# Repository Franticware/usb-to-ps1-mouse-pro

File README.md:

# usb-to-ps1-mouse-pro

This is an adapter for connecting USB mouse to PS1. It emulates the original [SCPH-1090 PlayStation Mouse](https://en.wikipedia.org/wiki/PlayStation_Mouse).

It can also convert [keyboard key presses to controller button presses](https://franticware.github.io/usb-to-ps1-mouse-pro/keyboard.html).

## Availability

[Check here](https://www.franticware.com/usb-to-ps1-mouse-pro-availability) whether the adapter is available for purchase.

## Firmware

The firmware is written mostly in C. It depends on [Raspberry Pi Pico SDK](https://github.com/raspberrypi/pico-sdk).

For a guide on how to update the firmware, see [Flashing the Firmware](https://franticware.github.io/usb-to-ps1-mouse-pro/flashing.html).

## Hardware

See [kicad](kicad) subdirectory for schematics and PCB design files. Alternatively, check [wiring](wiring) subdirectory for laymen-friendly picture guide or if you are looking to rewire your older [usb-to-playstation-mouse](https://github.com/Franticware/usb-to-playstation-mouse) adapter.

## Enclosure

The enclosure is intended for the PCB-based variant. The handwired one will not fit.

Printing in clear PETG is recommended.

3D model: https://www.printables.com/model/914178-official-enclosure-for-usb-to-ps1-mouse-pro

## Notes

* Important:
  * Make sure the USB device is rated for 100 mA or less (most USB mice and keyboards are). Do not connect devices with higher (or unspecified) current draw.
* Known issues:
  * Fixed in PCB_3: Incompatible with PSOne (SCPH-10X), where there are issues such as game stuttering and console reset.
  * In rare cases, Lemmings might pause during gameplay.
  * USB mouse compatibility is not 100%. The same applies to USB keyboards.
* Gameplay video:

## References - GitHub

This project would not be possible without these. Please go give them a star.

https://github.com/sekigon-gonnoc/Pico-PIO-USB

https://github.com/listff/hidparser

## Support this project

To help this project, you can go listen to or even buy a [music track of mine](https://share.amuse.io/track/vojtech-salajka-color-graphics-pinball-original-game-soundtrack) via your favorite service. It is not much, but it is the only digital product I am currently offering commercially as of writing this. Thank you!

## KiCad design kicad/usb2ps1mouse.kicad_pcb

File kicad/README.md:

## BOM

|Reference|Value|Datasheet|Footprint|Qty||
|-|-|-|-|-|-|
|C1, C2|10u/16V|~|Capacitor_SMD:C_1206_3216Metric|2||
|J1|Conn_01x09_Pin|~|PS1:Controller_THT90|1||
|J2|USB_A| ~|usb2ps1mouse-specific:USB_A_Sunken|1||
|J3|Conn_01x02|~|Jumper:SolderJumper-2_P1.3mm_Open_RoundedPad1.0x1.5mm|1|Short|
|J4|Conn_01x02|~|Jumper:SolderJumper-2_P1.3mm_Open_RoundedPad1.0x1.5mm|1|Do not short|
|R1, R2|22R|~|Resistor_SMD:R_0603_1608Metric|2||
|U1|RP2040-Zero||RP2040_Board:RP2040-Zero|1||
|U3|AMS1117-5.0|http://www.advanced-monolithic.com/pdf/ds1117.pdf|Package_TO_SOT_SMD:SOT-223-3_TabPin2|1||
||M3x10 countersunk screw + M3 nut|||1+1||

## Manufacturing

I have had the boards made at https://jlcpcb.com using the following parameters:

- PCB Thickness: 1.6
- PCB Color: Black
- Silkscreen: White
- Material Type: FR4
- Via Covering: Tented
- Surface Finish: LeadFree HASL
- Outer Copper Weight: 1 oz
- Board Outline Tolerance: ±0.2mm (Regular)

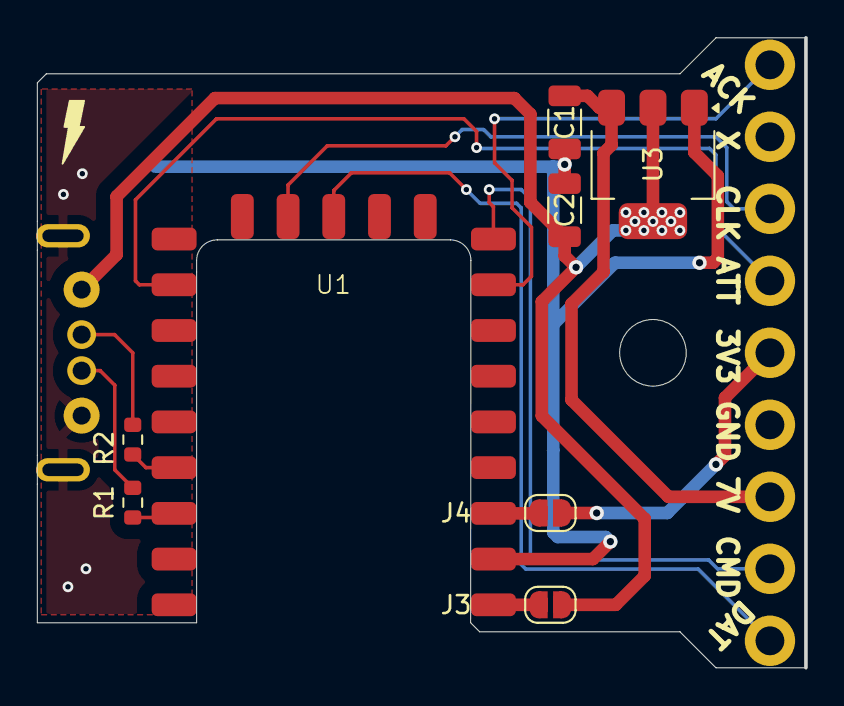
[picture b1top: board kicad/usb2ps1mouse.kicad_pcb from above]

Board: 2 copper layers, 42.6 x 35.0 mm, 11 parts (1 on the bottom side), 15 nets.

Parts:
C1, C2: 10u/16V; C_1206_3216Metric
H1: MountingHole; MountingHole_3.7mm
J1: Conn_01x09_Pin; Controller_THT90
J2: USB_A; USB_A_Sunken
J3, J4: Conn_01x02; SolderJumper-2_P1.3mm_Open_RoundedPad1.0x1.5mm
R1, R2: 22R; R_0603_1608Metric
U1: RP2040-Zero
U3: AMS1117-5.0; SOT-223-3_TabPin2

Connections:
+5V: C2.1, J2.1 (VBUS), J3.1, U3.2 (VO)
ACK: J1.9, U1.16 (15)
ATT: J1.6, U1.8 (7)
CLK: J1.7, U1.11 (10)
CMD: J1.2, U1.15 (14)
DATA: J1.1, U1.12 (11)
DM: J2.2 (D-), R2.1
DP: J2.3 (D+), R1.1
GND: C1.2, C2.2, J1.4, J2.4 (GND), J2.5 (Shield), U1.22 (GND), U3.1 (GND)
unnamed: J3.2, U1.23 (5V)
unnamed: J4.2, U1.21 (3V3)
unnamed: R1.2, U1.3 (2)
unnamed: R2.2, U1.4 (3)
VCON: J1.5, J4.1
VMOT: C1.1, J1.3, U3.3 (VI)

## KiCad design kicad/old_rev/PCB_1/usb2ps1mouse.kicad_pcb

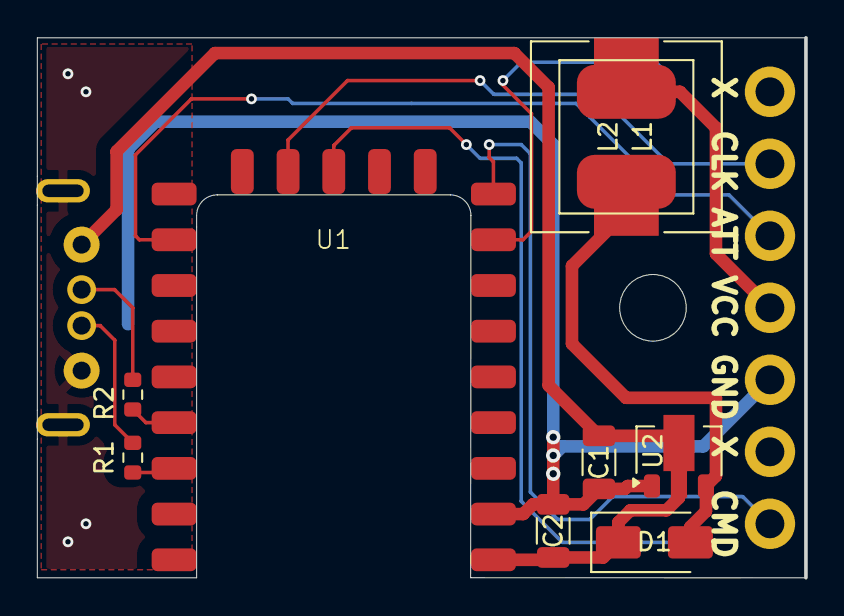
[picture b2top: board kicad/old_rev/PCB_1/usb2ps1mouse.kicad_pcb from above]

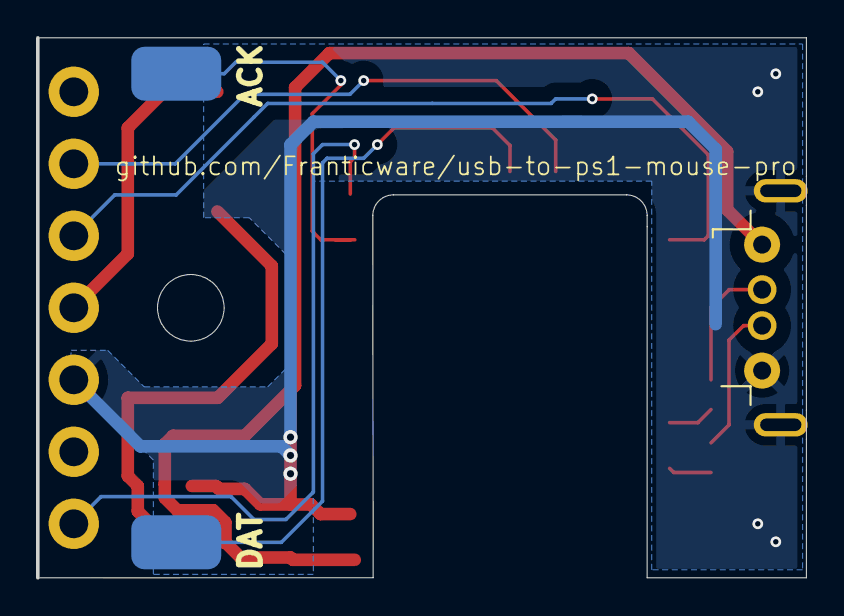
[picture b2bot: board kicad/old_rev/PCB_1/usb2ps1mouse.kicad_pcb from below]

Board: 2 copper layers, 42.6 x 30.0 mm, 14 parts (3 on the bottom side), 13 nets.

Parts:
C1, C2: 10u/16V; C_1206_3216Metric
D1: SS14; D_SMA
H1: MountingHole; MountingHole_3.7mm
J1: Conn_01x07_Pin; Controller_THT90
J2, J3: Conn_01x01_Pin; DSCON_pad
J4: USB_A; USB_A_Sunken
L1: 220; L_10.4x10.4_H4.8
L2: 220; L_Sumida_CR75
R1, R2: 22R; R_0603_1608Metric
U1: RP2040-Zero
U2: ME2108A50PG; SOT-89-3

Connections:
+5V: C1.1, C2.1, D1.1 (K), J4.1 (VBUS), U1.23 (5V), U2.2 (Vout)
ACK: J2.1, U1.16 (15)
ATT: J1.5, U1.8 (7)
CLK: J1.6, U1.11 (10)
CMD: J1.1, U1.15 (14)
DATA: J3.1, U1.12 (11)
DM: J4.2 (D-), R2.1
DP: J4.3 (D+), R1.1
GND: C1.2, C2.2, J1.3, J4.4 (GND), J4.5 (Shield), U1.22 (GND), U2.1 (Vss)
unnamed: D1.2 (A), L1.2, L2.2, U2.3 (Lx)
unnamed: R1.2, U1.3 (2)
unnamed: R2.2, U1.4 (3)
VCON: J1.4, L1.1, L2.1

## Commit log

2024-06-01 Add sorce code
2024-06-02 Register all button state changes, keep data until fully transmitted.
2024-06-02 Extend mouse support
2024-06-09 Add KiCad project
2024-06-09 Move firmware sources to src
2024-06-16 Update readme.
2024-06-16 Rename target.
2024-06-20 Update schematic
    Add BOM
2024-06-22 Add guide for handwired variant
2024-06-22 Add wiring diagram for RP2040-Zero
2024-08-06 Set slow slew rate for outputs
2024-09-01 Refactor and code simplification.
    Timeout for autoflash zenity dialog.
2024-09-01 Add RGB LED indication.
2024-09-07 Reduce RGB LED's initial green flash.
    Add forgotten RGB LED driver.
2024-09-08 Fix DAT access consistency
2024-09-10 Change RGB LED color scheme.
    Fix stray stdio_flush
2024-09-10 Light up RGB LED from the start
2024-09-15 Add usb-keyboard-to-ps1-controller
2024-10-11 Add gameplay video
2024-12-05 Move old PCB revision
2024-12-05 Add PCB_2 revision
2024-12-28 Add Flashing the Firmware document
2024-12-28 Add Readme for kicad files
2024-12-28 Add clarification
2024-12-28 Fix typo
2025-02-06 Add known issue to README.md
2025-04-25 Start over with updated libraries.
2025-04-25 Get rid of CDC USB device.
2025-04-26 Add ws2812 library from pico-examples
2025-04-26 Add working example of PIO ws2812
2025-04-27 Fix output byte format, update autoflash
2025-05-13 Log report data in json format.
2025-07-01 Controller state machine.
2025-07-02 Update RGB LED handling.
2025-07-02 Mouse sort of works, but keeps disconnecting.
2025-07-04 Disable debug output.
2025-07-04 Working mouse and keyboard.
2025-07-04 Add pico-sdk hotfix.
2025-07-04 Add PCB_3 board revision.
2025-07-04 Update BOM.
2025-07-05 Add PCB photo.
2025-07-07 Update wiring to match PCB_3.
2025-08-07 Refactor
2025-08-08 Extend keyboard mapping of select and start
2025-08-08 Add keyboard documentation stub
2025-08-16 Add keyboard mapping
2025-08-16 Fix readme, revert debug code
